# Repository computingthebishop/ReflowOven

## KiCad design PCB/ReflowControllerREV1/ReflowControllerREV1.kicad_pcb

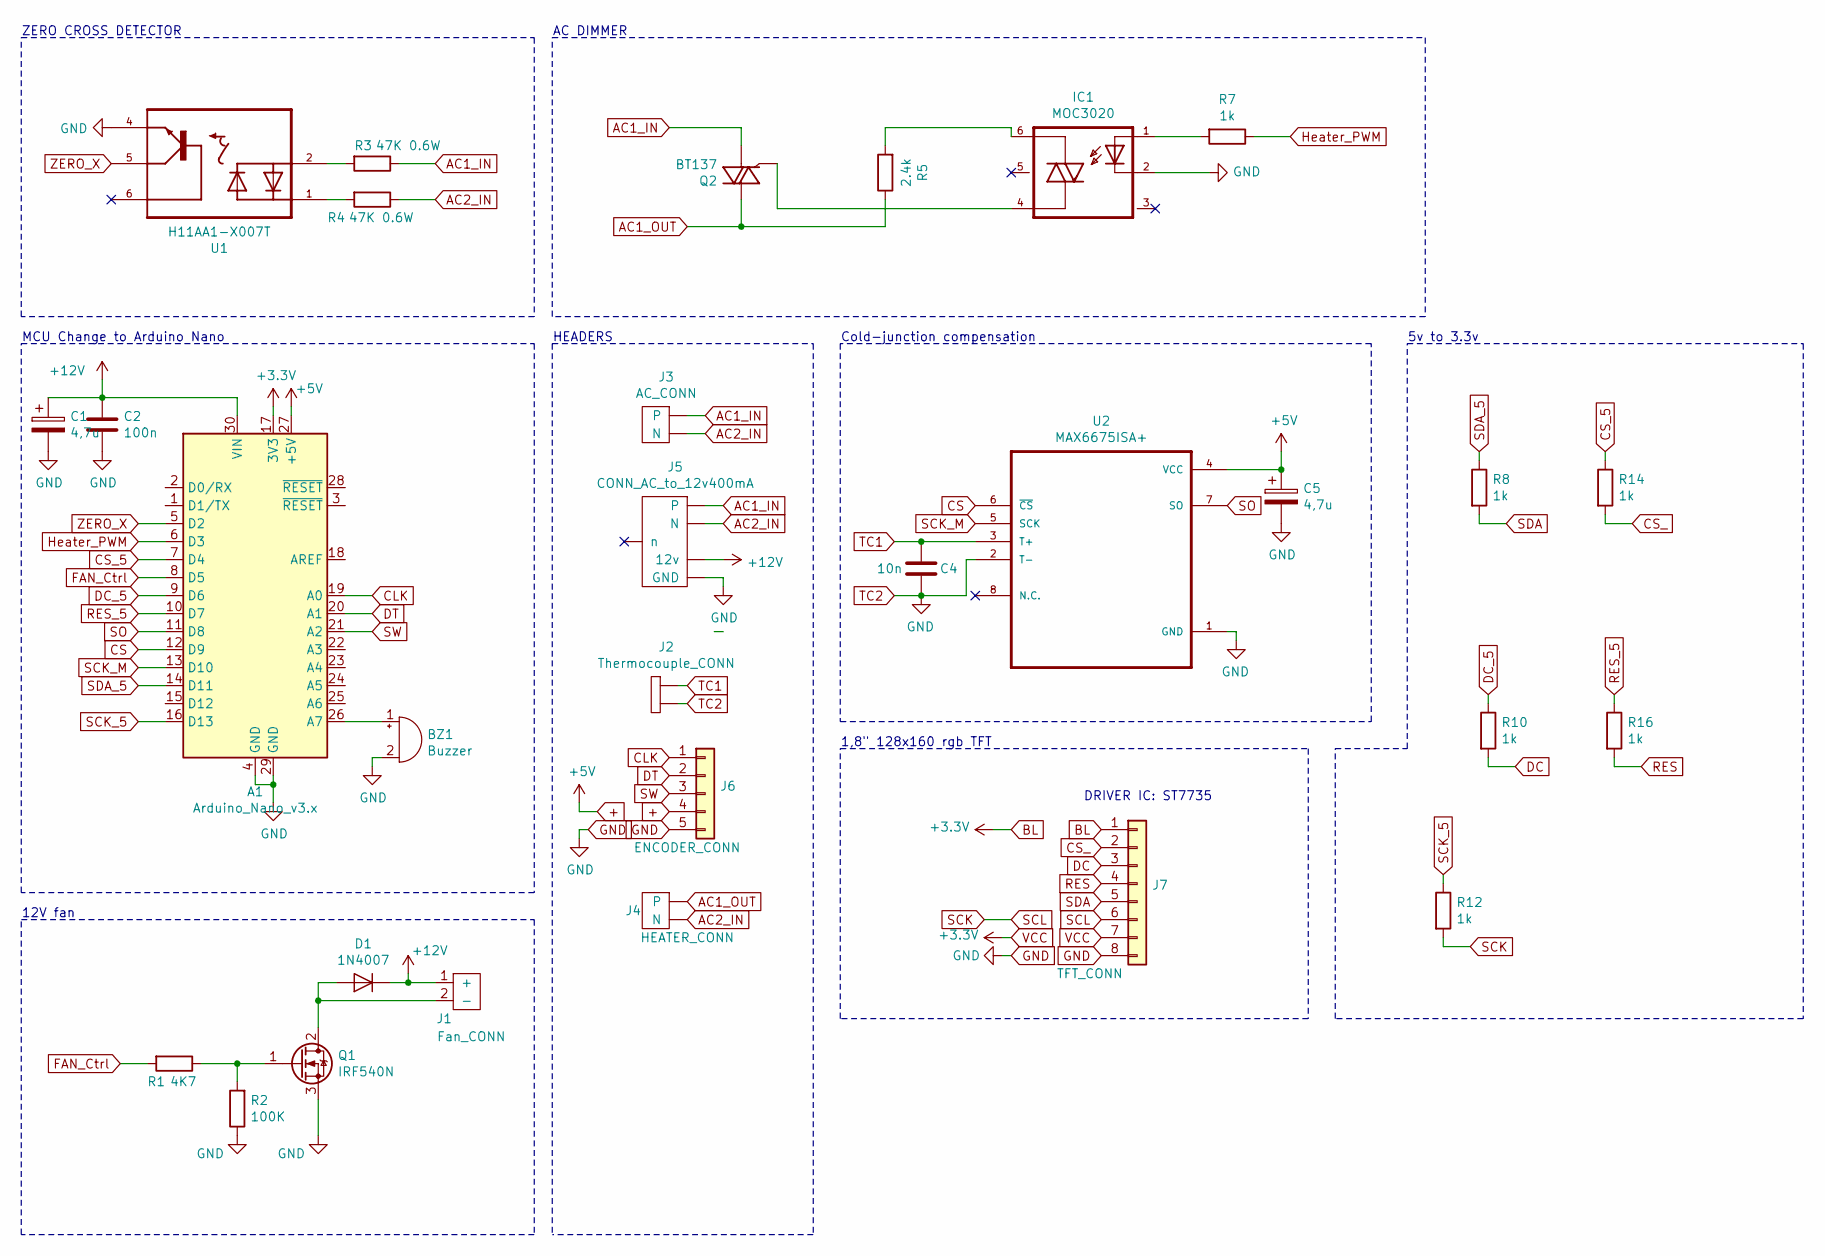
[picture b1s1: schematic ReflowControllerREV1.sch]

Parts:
A1: Arduino_Nano_v3.x; Arduino_Nano
BZ1: Buzzer; PinHeader_1x02_P2.54mm_Vertical
C1, C5: 4,7u; C_Elec_4x5.8
C2: 100n; C_0805_2012Metric_Pad1.15x1.40mm_HandSolder
C4: 10n; C_0805_2012Metric_Pad1.15x1.40mm_HandSolder
D1: 1N4007; D_DO-41_SOD81_P10.16mm_Horizontal
IC1: MOC3020; DIP-6_W7.62mm
J1: Fan_CONN; JST_EH_B2B-EH-A_1x02_P2.50mm_Vertical
J2: Thermocouple_CONN; PinHeader_1x02_P2.54mm_Vertical
J3: AC_CONN; TerminalBlock_bornier-2_P5.08mm
J4: HEATER_CONN; TerminalBlock_bornier-2_P5.08mm
J5: CONN_AC_to_12v400mA; 12v220
J6: ENCODER_CONN; PinSocket_1x05_P2.54mm_Horizontal
J7: TFT_CONN; PinSocket_1x08_P2.54mm_Horizontal
Q1: IRF540N; TO-263-3_TabPin4
Q2: BT137; TO-220-3_Horizontal_TabUp
R1: 4K7; R_0805_2012Metric_Pad1.15x1.40mm_HandSolder
R2: 100K; R_0805_2012Metric_Pad1.15x1.40mm_HandSolder
R3, R4: 47K 0.6W; R_Axial_DIN0207_L6.3mm_D2.5mm_P10.16mm_Horizontal
R5: 2.4k; R_0805_2012Metric_Pad1.15x1.40mm_HandSolder
R7, R8, R10, R12, R14, R16: 1k; R_0805_2012Metric_Pad1.15x1.40mm_HandSolder
U1: H11AA1-X007T; DIP-6_W7.62mm_LongPads
U2: MAX6675ISA+; SOIC-8-1EP_3.9x4.9mm_P1.27mm_EP2.29x3mm

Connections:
+: A1.27 (+5V), C5.1, J6.4, U2.4 (VCC)
+12V: A1.30 (VIN), C1.1, C2.1, D1.1 (K), J1.1 (+), J5.5 (12v)
AC1_IN: J3.1, J5.1, Q2.1 (MT1), R3.1
AC1_OUT: J4.1, Q2.2 (MT2), R5.1
AC2_IN: J3.2 (N), J4.2 (N), J5.2 (N), R4.1
BL: A1.17 (3V3), J7.1, J7.7
CLK: A1.19 (A0), J6.1
CS: A1.12 (D9), U2.6 (~CS~)
CS_: J7.2, R14.2
CS_5: A1.7 (D4), R14.1
DC: J7.3, R10.2
DC_5: A1.9 (D6), R10.1
DT: A1.20 (A1), J6.2
FAN_Ctrl: A1.8 (D5), R1.2
GND: A1.4 (GND), A1.29 (GND), BZ1.2 (+), C1.2, C2.2, C4.2, C5.2, IC1.2 (C), J2.2, J5.3 (GND), J6.5, J7.8, Q1.3 (S), R2.1, U1.4 (E), U2.1 (GND), U2.2 (T-)
Heater_PWM: A1.6 (D3), R7.1
unnamed: A1.26 (A7), BZ1.1 (-)
unnamed: D1.2 (A), J1.2 (-), Q1.2 (D)
unnamed: IC1.1 (A), R7.2
unnamed: IC1.4 (A1), Q2.3 (G)
unnamed: IC1.6 (A2), R5.2
unnamed: Q1.1 (G), R1.1, R2.2
unnamed: R3.2, U1.2 (C/A)
unnamed: R4.2, U1.1 (A/C)
RES: J7.4, R16.2
RES_5: A1.10 (D7), R16.1
SCK: J7.6, R12.2
SCK_5: A1.16 (D13), R12.1
SCK_M: A1.13 (D10), U2.5 (SCK)
SDA: J7.5, R8.2
SDA_5: A1.14 (D11), R8.1
SO: A1.11 (D8), U2.7 (SO)
SW: A1.21 (A2), J6.3
TC1: C4.1, J2.1, U2.3 (T+)
ZERO_X: A1.5 (D2), U1.5 (C)

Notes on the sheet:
ZERO CROSS DETECTOR
AC DIMMER
HEADERS
Cold-junction compensation
MCU Change to Arduino Nano
12V fan
1,8" 128x160 rgb TFT
DRIVER IC: ST7735
5v to 3.3v

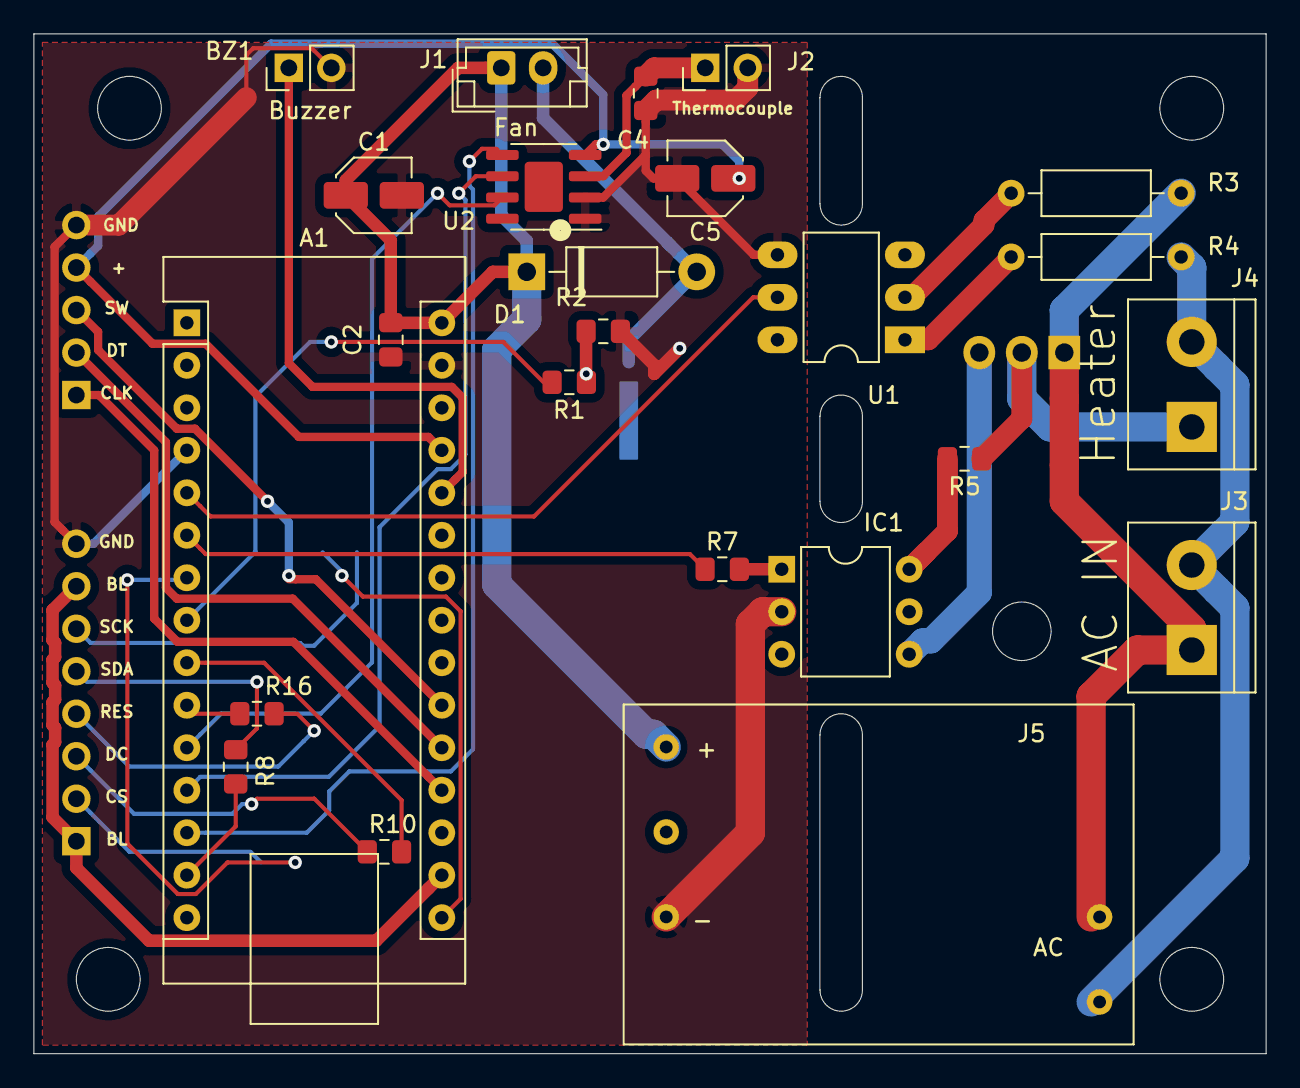
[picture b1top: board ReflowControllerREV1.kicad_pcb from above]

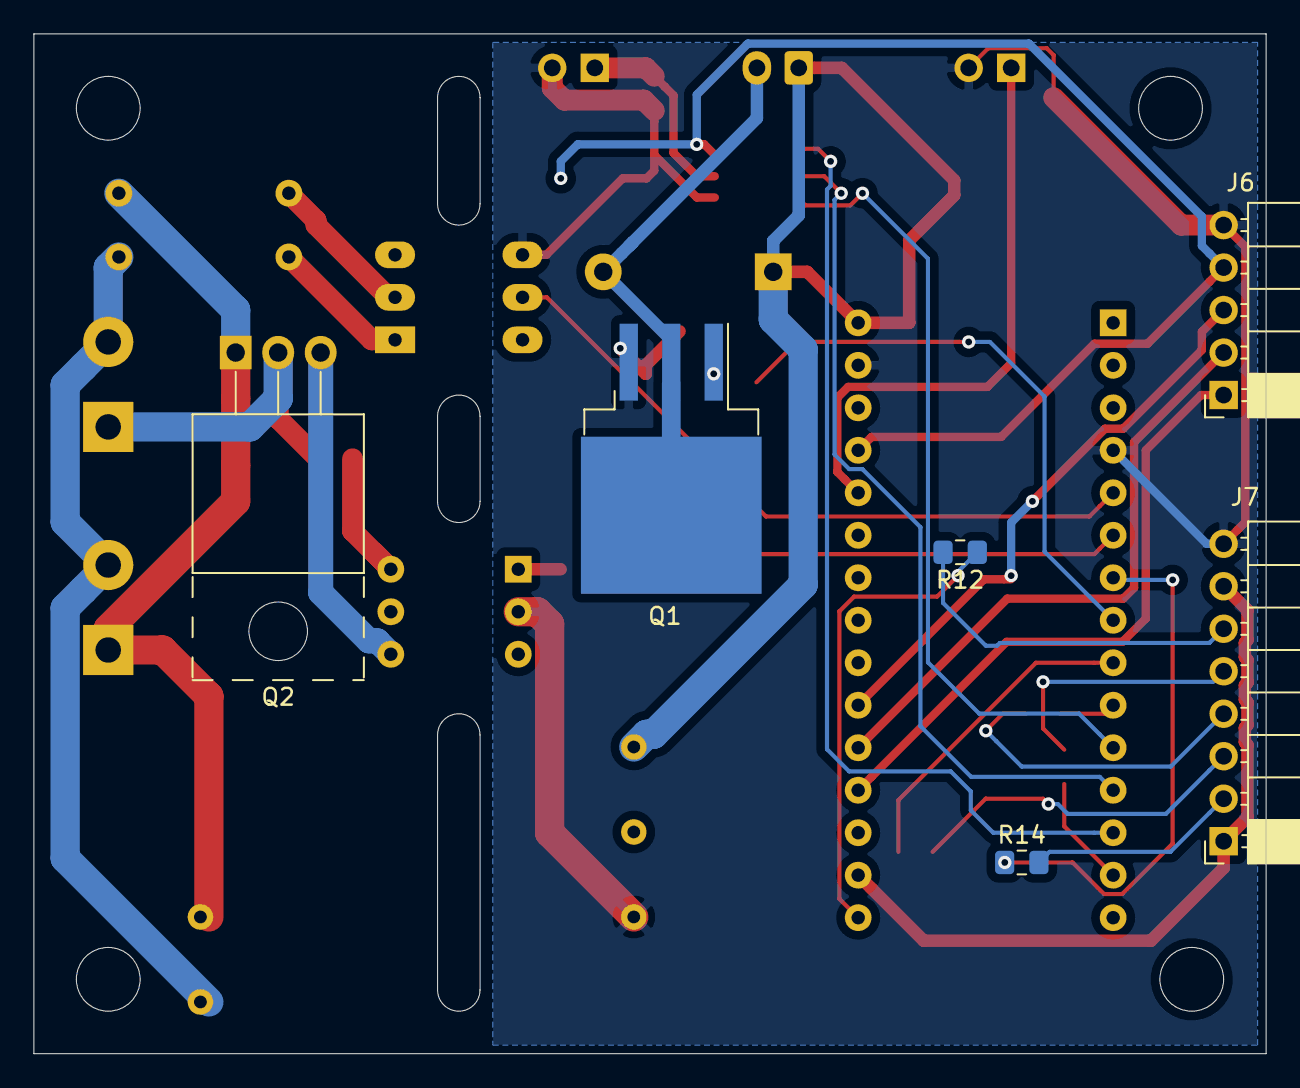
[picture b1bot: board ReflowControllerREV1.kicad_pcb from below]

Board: 2 copper layers, 73.7 x 61.0 mm, 30 parts (6 on the bottom side), 35 nets.

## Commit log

2019-05-30 pcb created
2019-06-23 Lib Created
2019-06-26 cad created
2019-11-02 REV1 finished
2019-11-03 Gerbers generated
2019-11-12 small pcb tweaKs
2019-11-19 pdf created
2019-12-26 firmware finished
2020-01-03 cuts on aluminum
2020-06-30 cad finished
2020-06-30 schematic updated
2020-06-30 final pcb
2020-08-03 pdf and step
